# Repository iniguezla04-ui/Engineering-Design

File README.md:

# Engineering-Design
Senior Design Project
Product: Electric Skateboard
Description: Hands-free electric skateboard design that uses gyroscope, accelerometer, and custom ESC

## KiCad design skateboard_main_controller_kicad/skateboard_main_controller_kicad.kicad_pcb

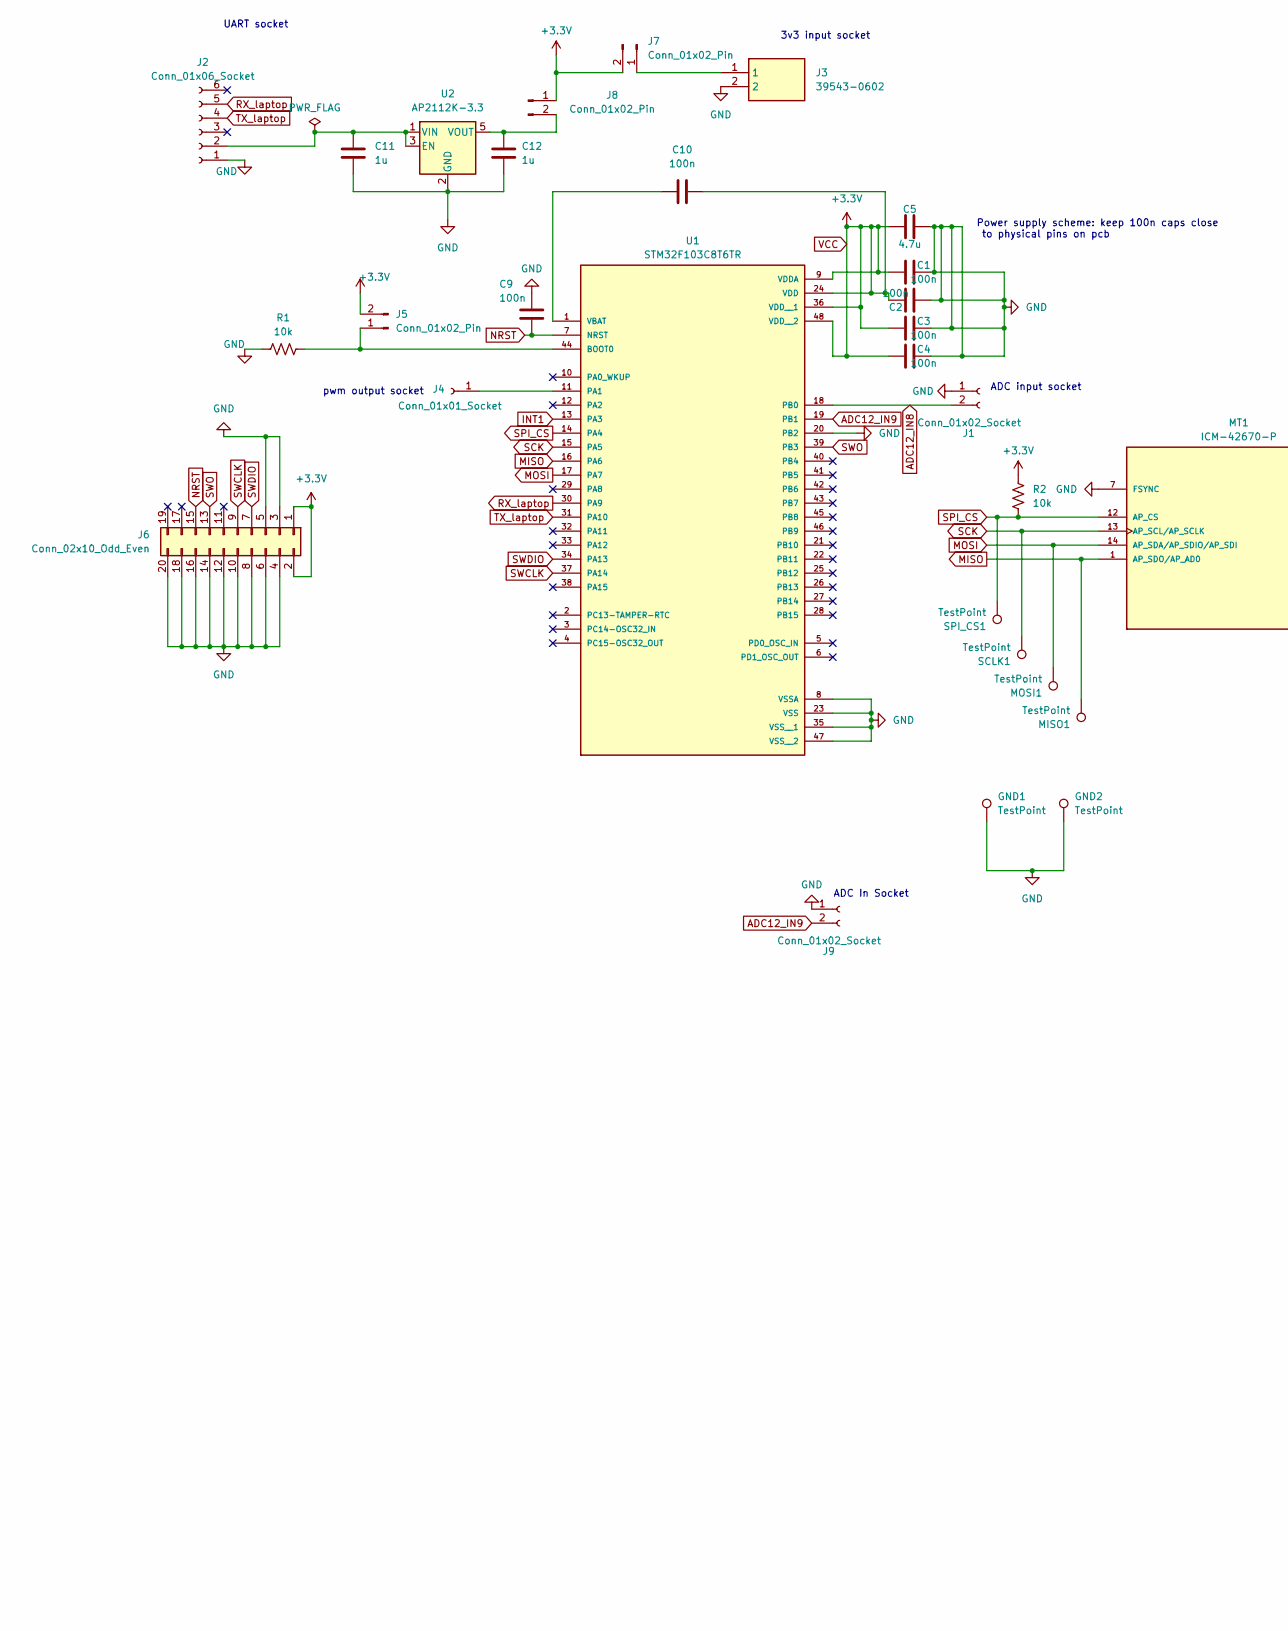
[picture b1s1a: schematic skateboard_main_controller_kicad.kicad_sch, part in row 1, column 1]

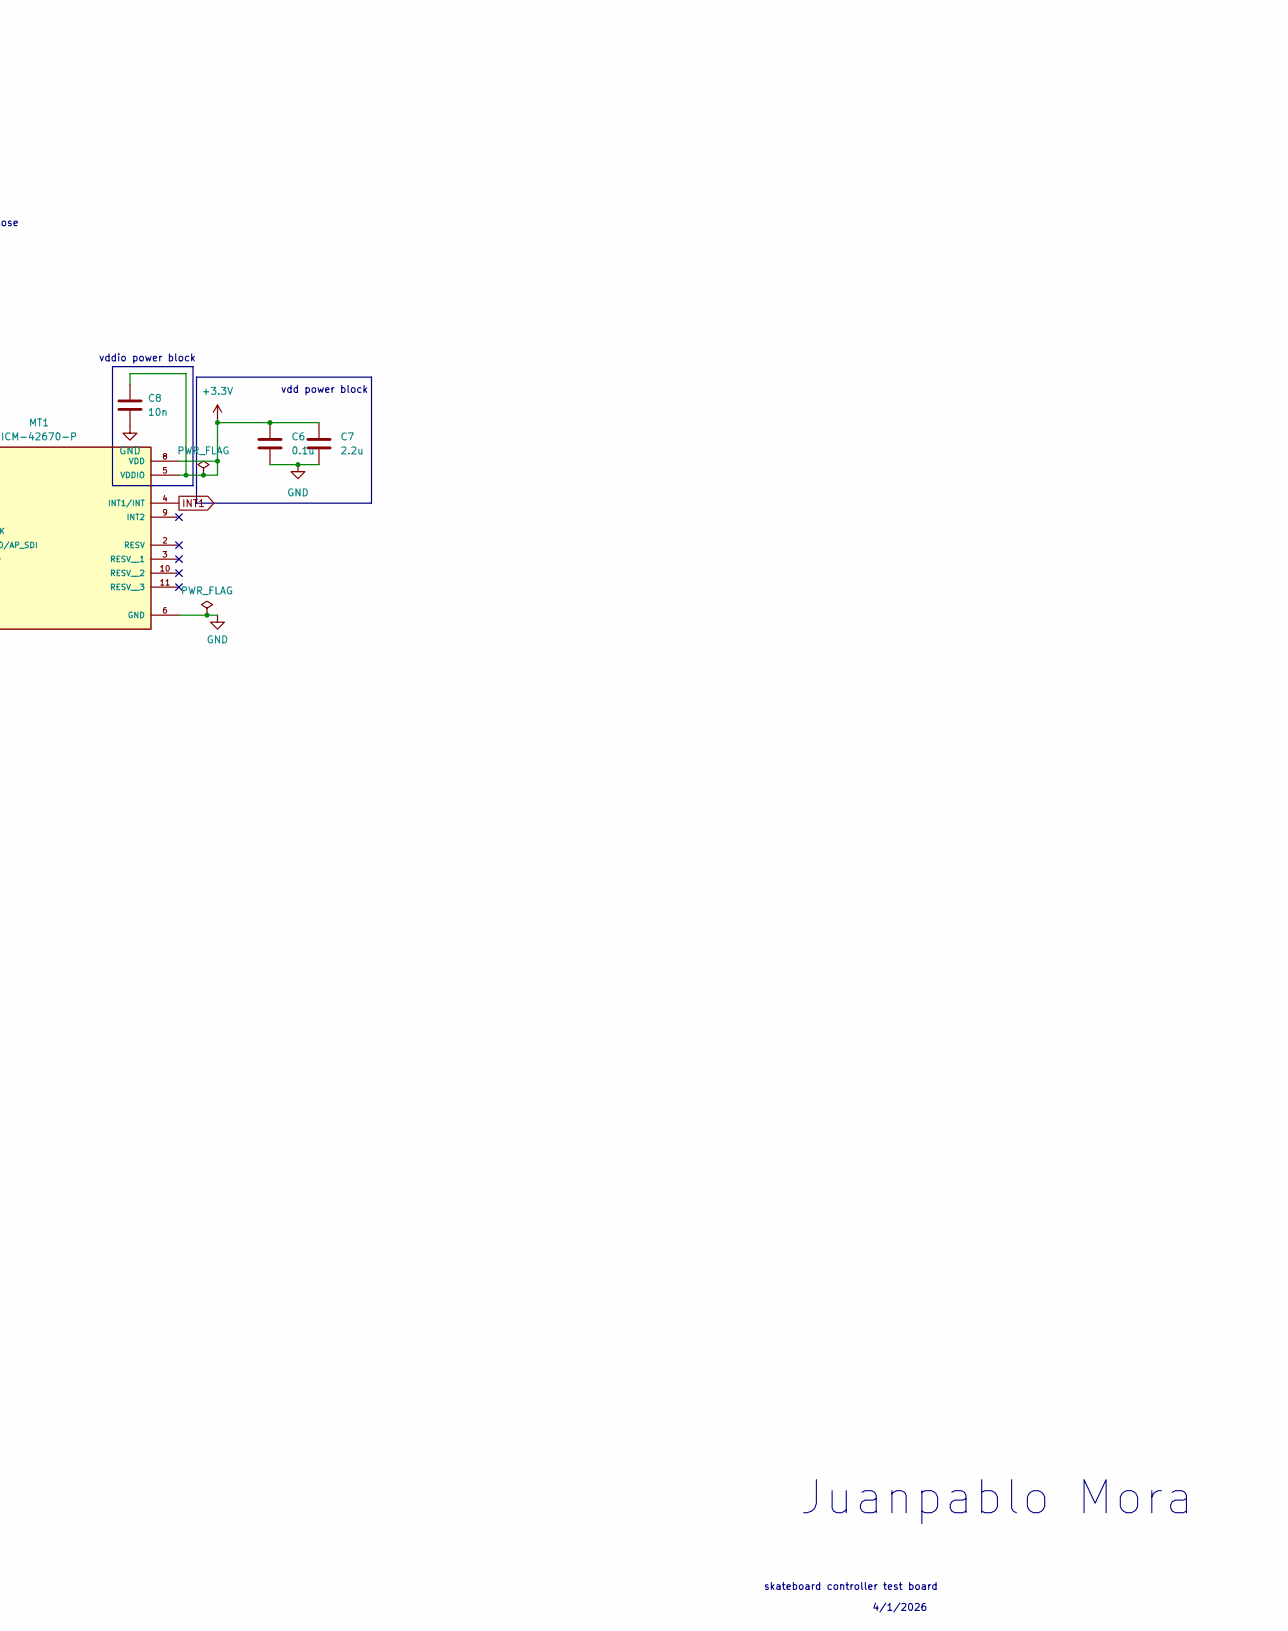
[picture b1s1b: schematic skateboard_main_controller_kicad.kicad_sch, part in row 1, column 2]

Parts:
C1, C2, C3, C4, C9, C10: 100n; C_0805_2012Metric
C5: 4.7u; C_0805_2012Metric
C6: 0.1u; C_0805_2012Metric
C7: 2.2u; C_0805_2012Metric
C8: 10n; C_0805_2012Metric
C11, C12: 1u; C_0805_2012Metric
GND1, GND2: TestPoint; TestPoint_Keystone_5010-5014_Multipurpose
J1, J9: Conn_01x02_Socket; PinHeader_1x02_P2.54mm_Vertical
J2: Conn_01x06_Socket; PinHeader_1x06_P2.54mm_Vertical
J3: 39543-0602; SHDR2W100P0X500_1X2_1000X760X1040P; Mouser Part Number 538-39543-0602
J4: Conn_01x01_Socket; PinHeader_1x01_P2.54mm_Vertical
J5: Conn_01x02_Pin
J6: Conn_02x10_Odd_Even; PinHeader_2x10_P2.54mm_Vertical
J7, J8: Conn_01x02_Pin; PinHeader_1x02_P2.54mm_Vertical
MISO1: TestPoint; TestPoint_Keystone_5010-5014_Multipurpose
MOSI1: TestPoint; TestPoint_Keystone_5010-5014_Multipurpose
MT1: ICM-42670-P; XDCR_ICM-42670-P; PARTREV 1.1
R1, R2: 10k; R_0805_2012Metric
SCLK1: TestPoint; TestPoint_Keystone_5010-5014_Multipurpose
SPI_CS1: TestPoint; TestPoint_Keystone_5010-5014_Multipurpose
U1: STM32F103C8T6TR; QFP50P900X900X160-48N; PARTREV 10
U2: AP2112K-3.3; SOT-23-5

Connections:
ADC12_IN8: J1.2, U1.18 (PB0)
ADC12_IN9: J9.2, U1.19 (PB1)
GND: C1.2, C2.2, C3.2, C4.2, C5.2, C6.2, C7.2, C8.2, C9.1, C11.2, C12.2, GND1.1 (1_1), GND2.1 (1_1), J1.1, J2.1, J3.2, J6.3, J6.4, J6.5, J6.6, J6.8, J6.10, J6.12, J6.14, J6.16, J6.18, J6.20, J9.1, MT1.6 (GND), MT1.7 (FSYNC), R1.1, U1.8 (VSSA), U1.20 (PB2), U1.23 (VSS), U1.35 (VSS__1), U1.47 (VSS__2), U2.2 (GND)
INT1: MT1.4 (INT1/INT), U1.13 (PA3)
MISO: MISO1.1 (1_1), MT1.1 (AP_SDO/AP_AD0), U1.16 (PA6)
MOSI: MOSI1.1 (1_1), MT1.14 (AP_SDA/AP_SDIO/AP_SDI), U1.17 (PA7)
NRST: C9.2, J6.15, U1.7 (NRST)
unnamed: C11.1, J2.2, U2.1 (VIN), U2.3 (EN)
unnamed: J4.1 (Pin_1_1), U1.11 (PA1)
unnamed: J5.1, R1.2, U1.44 (BOOT0)
unnamed: J3.1, J7.1
unnamed: C12.1, J8.2, U2.5 (VOUT)
unnamed: C10.1, U1.1 (VBAT)
RX_laptop: J2.5, U1.30 (PA9)
SCK: MT1.13 (AP_SCL/AP_SCLK), SCLK1.1 (1_1), U1.15 (PA5)
SPI_CS: MT1.12 (AP_CS), R2.2, SPI_CS1.1 (1_1), U1.14 (PA4)
SWCLK: J6.9, U1.37 (PA14)
SWDIO: J6.7, U1.34 (PA13)
SWO: J6.13, U1.39 (PB3)
TX_laptop: J2.4, U1.31 (PA10)
VCC: C1.1, C2.1, C3.1, C4.1, C5.1, C6.1, C7.1, C8.1, C10.2, J5.2, J6.1, J6.2, J7.2, J8.1, MT1.5 (VDDIO), MT1.8 (VDD), R2.1, U1.9 (VDDA), U1.24 (VDD), U1.36 (VDD__1), U1.48 (VDD__2)

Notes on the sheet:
ADC input socket
3v3 input socket
Power supply scheme: keep 100n caps close to physical pins on pcb
UART socket
4/1/2026
skateboard controller test board
vddio power block
pwm output socket
vdd power block
Juanpablo Mora
ADC In Socket

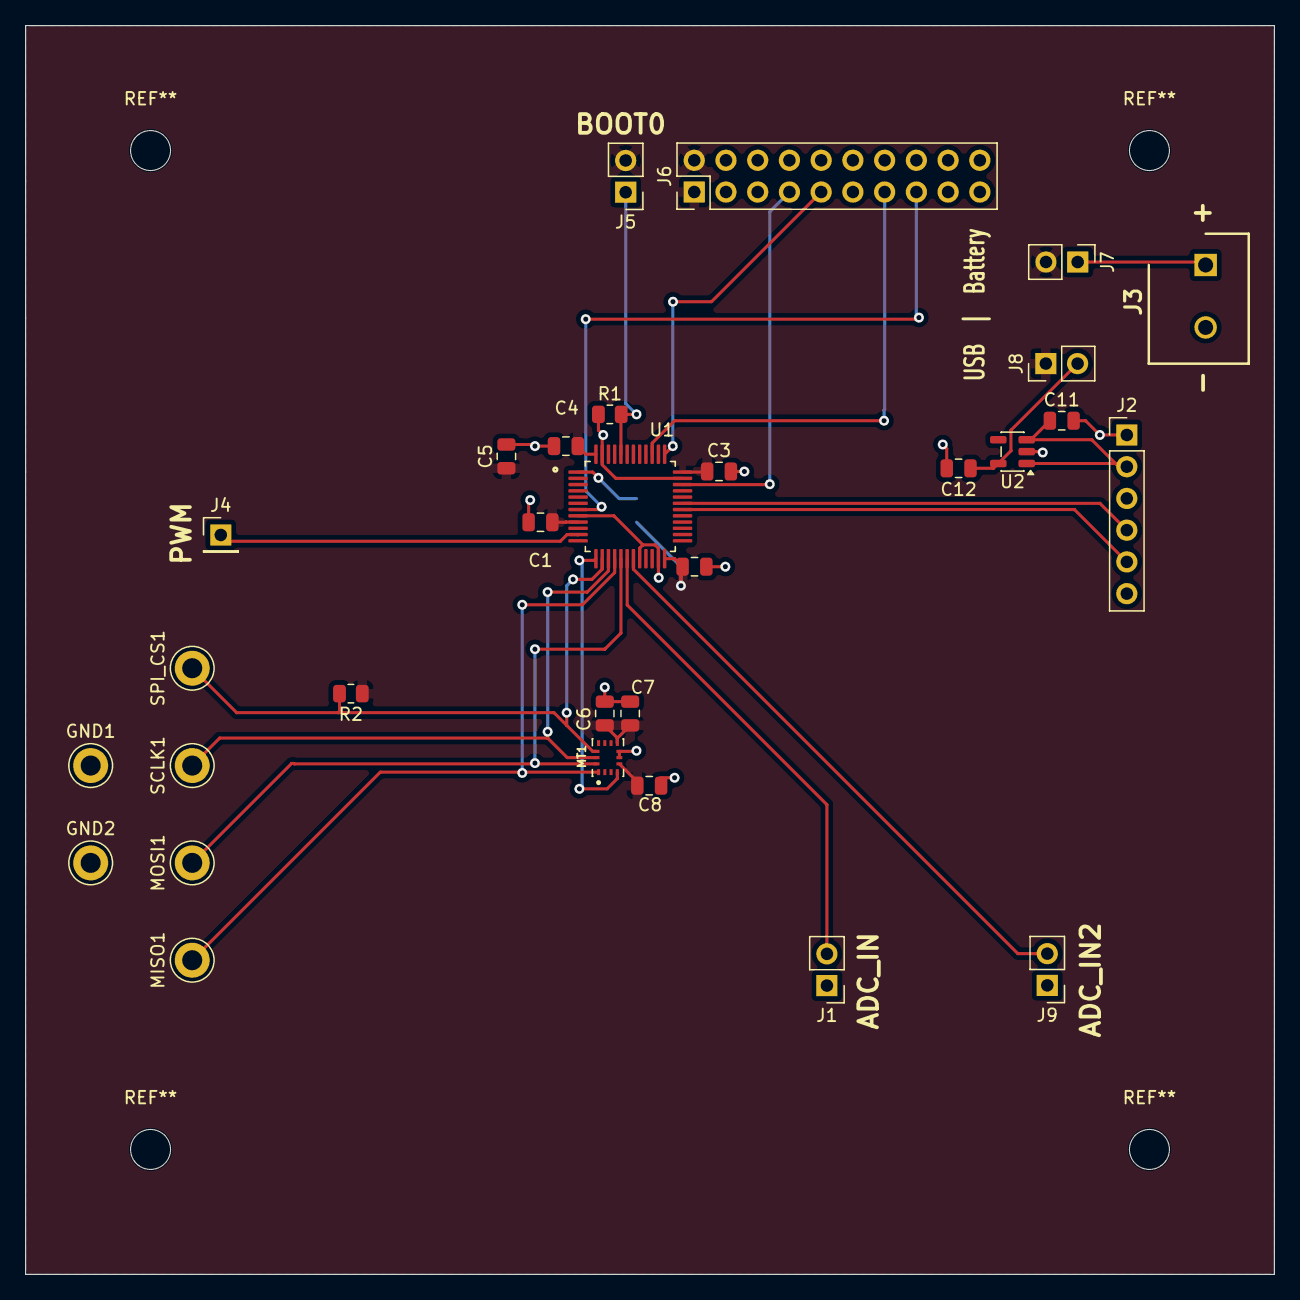
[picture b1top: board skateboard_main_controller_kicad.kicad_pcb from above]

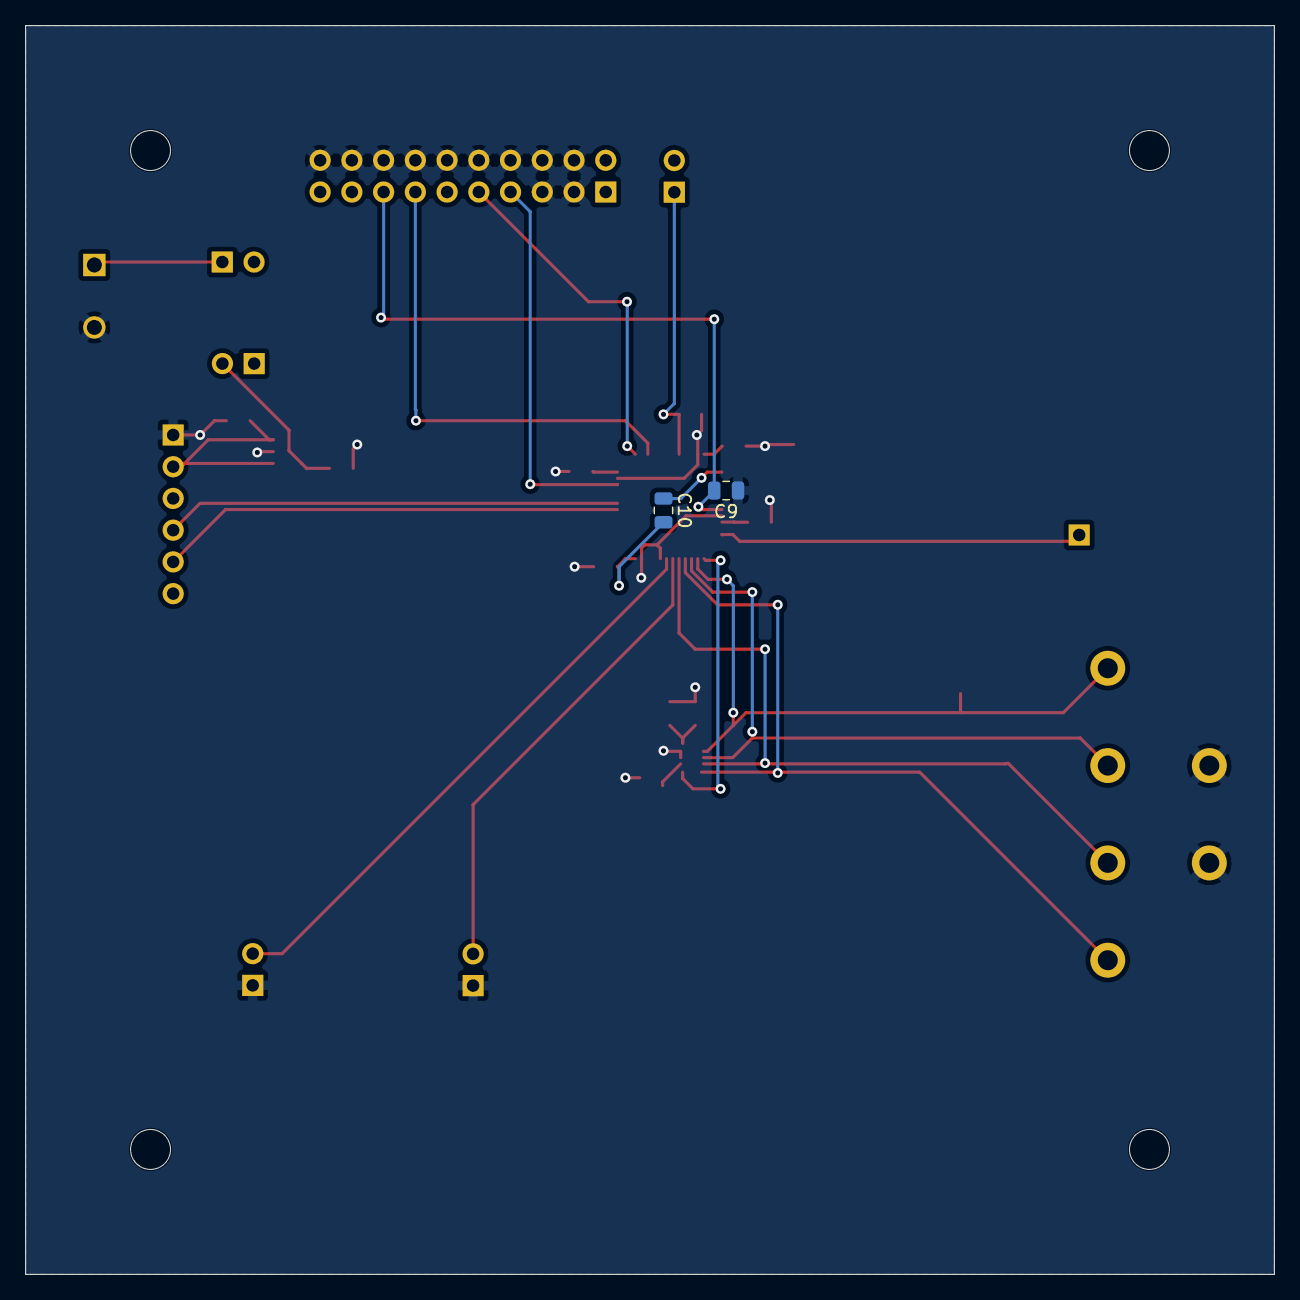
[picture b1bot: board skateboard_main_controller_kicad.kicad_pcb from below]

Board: 2 copper layers, 99.9 x 99.9 mm, 32 parts (2 on the bottom side), 21 nets.

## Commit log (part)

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2026-04-01 add kicad project
2026-04-01 Let there be light
2026-04-01 mv .gitignore
2026-04-01 add correct kicad files
2026-04-01 PCB initial commit
2026-04-04 hello
2026-04-05 JLKDJF
2026-04-12 Creating Makefile
2026-04-13 creating header
2026-04-13 fixing target order in Makefile
2026-04-13 creating startup target in Makefile
2026-04-13 adding startup.o prereq
2026-04-13 editting startup file,ld,Makefile
2026-04-14 build: change to startup file in c and change makefile accordingly
    use linker script from Artful Bytes
2026-04-14 add C runtime init (CRT0)
2026-04-14 move startup.c and ld to startup dir and edit Makefile accordingly
2026-04-14 Add usart1isr to isr table
2026-04-14 Begin usart driver and add include directories
2026-04-15 first commit of usart dirver
2026-04-15 Change ld-ram length 20kb -> 8kb
2026-04-15 enable global interrupts and usart interrupts
2026-04-15 usart.c changes
2026-04-15 fix ivt index for usart interrupt
2026-04-15 fix: make putChar call interrupt if it was waiting
2026-04-15 rm vscode files
2026-04-15 funny
